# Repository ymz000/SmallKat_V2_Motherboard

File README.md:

# SmallKat_V2 Motherboard

By Keion Bisland
  May 2018

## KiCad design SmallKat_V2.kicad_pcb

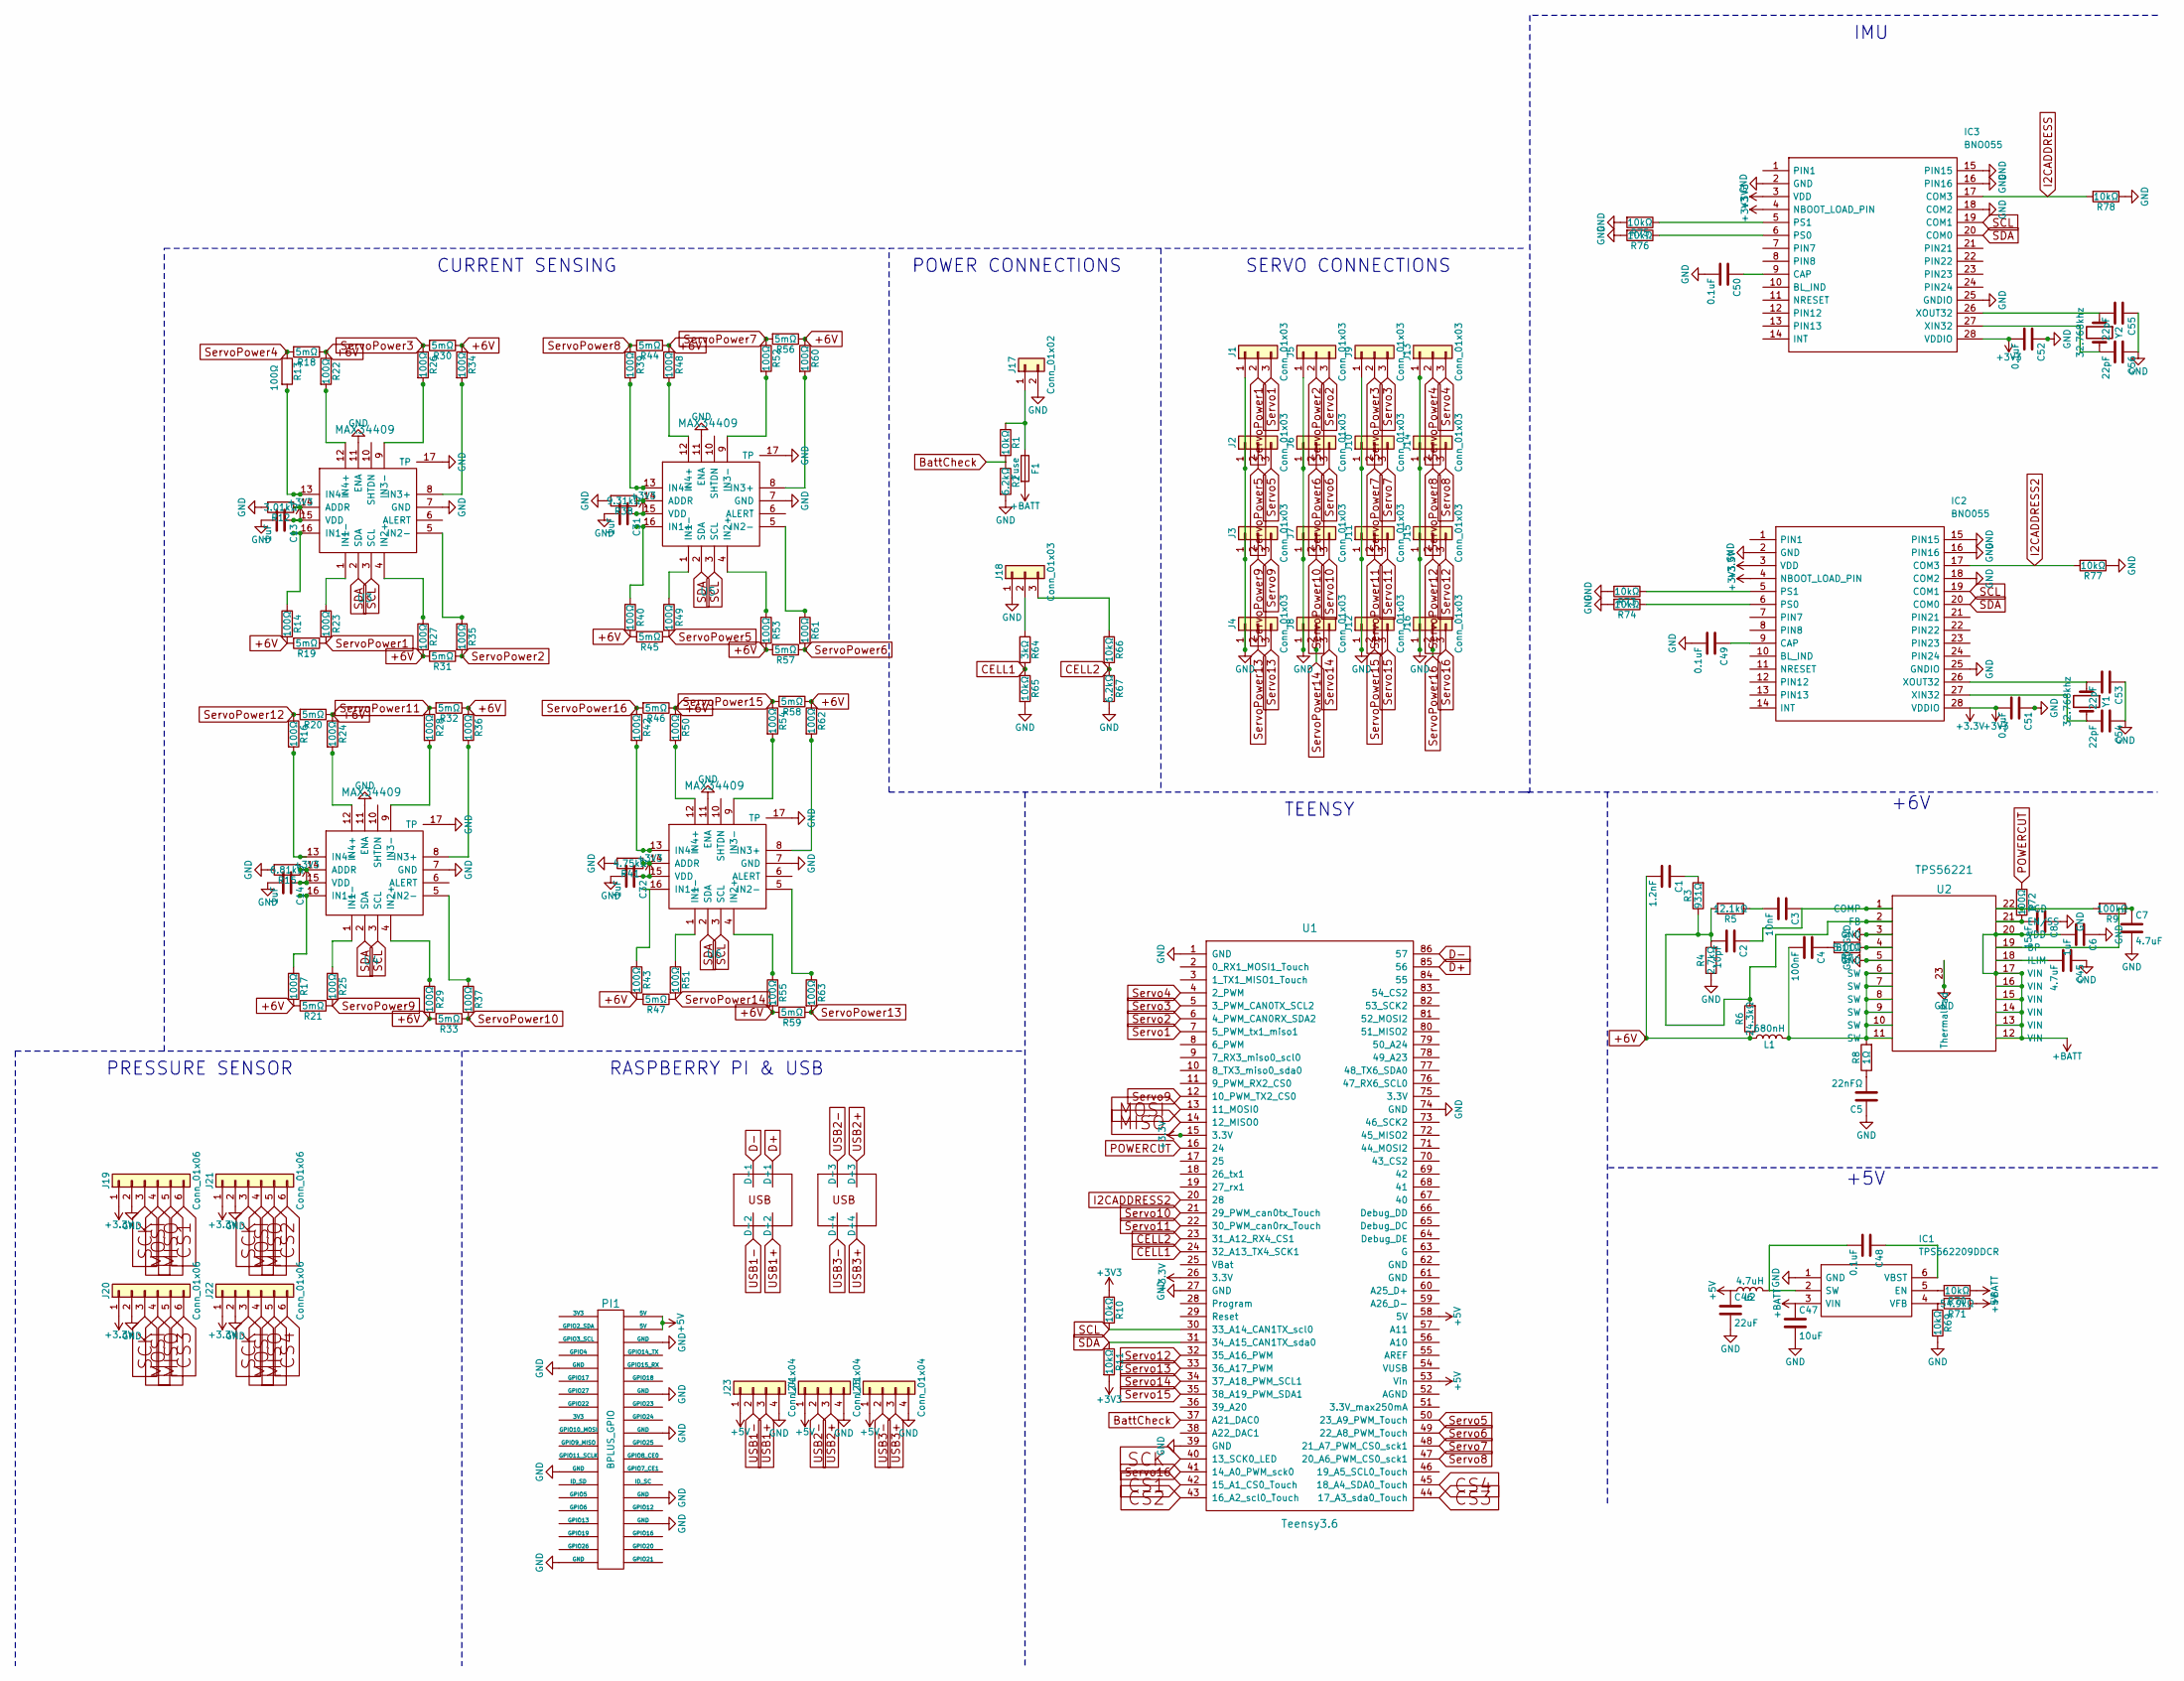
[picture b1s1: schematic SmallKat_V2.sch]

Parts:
C1: 1.2nF; C_0402
C2: 10pF; C_0402
C3: 10nF; C_0402
C4: 100nF; C_0402
C5: 22nFΩ; C_0402
C6: 1uF; C_0603
C7: 4.7uF; C_0603
C8: 15nF; C_0603
C13, C14, C31, C32: 1uF; C_0402
C45: 4.7uF; C_0402
C46: 22uF; C_0603
C47: 10uF; C_0402
C48, C49, C50, C51, C52: 0.1uF; C_0402
C53, C54, C55, C56: 22pF; C_0402
F1: Fuse; Fuse_SMD1206_Reflow
IC1: TPS562209DDCR; SOT95P280X110-6N; Manufacturer_Part_Number TPS562209DDCR
IC2, IC3: BNO055; Manufacturer_Part_Number BNO055
J1, J2, J3, J4, J5, J6, J7, J8, J9, J10, J11, J12, J13, J14, J15, J16, J18: Conn_01x03; Pin_Header_Straight_1x03_Pitch2.54mm
J17: Conn_01x02; Pin_Header_Straight_1x02_Pitch2.54mm
J19, J20, J21, J22: Conn_01x06; Pin_Header_Straight_1x06_Pitch1.00mm
J23, J24, J25: Conn_01x04; Pin_Header_Straight_1x04_Pitch2.00mm
L1: 680nH; L_7.3x7.3_H4.5
L2: 4.7uH; L_0805
PI1: BPLUS_GPIO; Pin_Header_Straight_2x20_Pitch2.54mm
R1, R10, R11, R65, R66, R69, R70, R73, R74, R75, R76, R77, R78: 10kΩ; R_0402
R2, R67: 6.2kΩ; R_0402
R3: 931Ω; R_0402
R4: 2.7kΩ; R_0402
R5: 12.1kΩ; R_0402
R6: 24.3kΩ; R_0402
R7: 5.11Ω; R_0402
R8: 1Ω; R_0402
R9: 100kΩ; R_0402
R12: 3.01kΩ; R_0402
R13, R14, R16, R17, R22, R23, R24, R25, R26, R27, R28, R29, R34, R35, R36, R37, R39, R40, R42, R43, R48, R49, R50, R51, R52, R53, R54, R55, R60, R61, R62, R63, R72: 100Ω; R_0402
R15: 6.81kΩ; R_0402
R18, R19, R20, R21, R30, R31, R32, R33, R44, R45, R46, R47, R56, R57, R58, R59: 5mΩ; R_1210
R38: 9.31kΩ; R_0402
R41: 4.75kΩ; R_0402
R64: 3kΩ; R_0402
R71: 54.9kΩ; R_0402
U1: Teensy3.6; Teensy35_36_custom_2
U2: TPS56221
U3, U4, U5, U6: MAX34409
Y1, Y2: 32.768khz; Crystal_SMD_3215-2pin_3.2x1.5mm

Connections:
+3V3: C13.1, C14.1, C31.1, C32.1, C51.2, C52.2, IC2.3 (VDD), IC2.4 (NBOOT_LOAD_PIN), IC2.28 (VDDIO), IC3.3 (VDD), IC3.4 (NBOOT_LOAD_PIN), IC3.28 (VDDIO), J19.1, J20.1, J21.1, J22.1, R10.1, R11.2, U1.15 (3.3V), U1.26 (3.3V), U3.15 (VDD), U4.15 (VDD), U5.15 (VDD), U6.15 (VDD)
+5V: C46.1, J23.1, J24.1, J25.1, L2.1, PI1.2 (5V), PI1.4 (5V), R71.1, U1.53 (Vin), U1.58 (5V)
+6V: C1.2, L1.1, R6.1, R14.2, R17.2, R18.1, R19.2, R20.1, R21.2, R22.1, R24.1, R27.2, R29.2, R30.1, R31.2, R32.1, R33.2, R34.1, R36.1, R40.2, R43.2, R44.1, R45.2, R46.1, R47.2, R48.1, R50.1, R53.2, R55.2, R56.1, R57.2, R58.1, R59.2, R60.1, R62.1
+BATT: C6.2, C47.1, F1.2, IC1.3 (VIN), R70.1, U2.12 (VIN), U2.13 (VIN), U2.14 (VIN), U2.15 (VIN), U2.16 (VIN), U2.17 (VIN), U2.20 (VDD)
BattCheck: R1.2, R2.1, U1.37 (A21_DAC0)
CELL1: R64.2, R65.1, U1.24 (32_A13_TX4_SCK1)
CELL2: R66.2, R67.1, U1.23 (31_A12_RX4_CS1)
CS1: J19.6, U1.42 (15_A1_CS0_Touch)
CS2: J21.6, U1.43 (16_A2_scl0_Touch)
CS3: J20.6, U1.44 (17_A3_sda0_Touch)
CS4: J22.6, U1.45 (18_A4_SDA0_Touch)
D+: PI1.42 (D+1), U1.85 (56)
D-: PI1.41 (D-1), U1.86 (57)
GND: C5.1, C6.1, C7.2, C8.1, C13.2, C14.2, C31.2, C32.2, C45.1, C46.2, C47.2, C49.2, C50.2, C51.1, C52.1, C53.1, C54.1, C55.1, C56.1, IC1.1 (GND), IC2.2 (GND), IC2.15 (PIN15), IC2.16 (PIN16), IC2.18 (COM2), IC2.25 (GNDIO), IC3.2 (GND), IC3.15 (PIN15), IC3.16 (PIN16), IC3.18 (COM2), IC3.25 (GNDIO), J1.1, J2.1, J3.1, J4.1, J5.1, J6.1, J7.1, J8.1, J9.1, J10.1, J11.1, J12.1, J13.1, J14.1, J15.1, J16.1, J17.2, J18.1, J19.2, J20.2, J21.2, J22.2, J23.4, J24.4, J25.4, PI1.6 (GND), PI1.9 (GND), PI1.14 (GND), PI1.20 (GND), PI1.25 (GND), PI1.30 (GND), PI1.34 (GND), PI1.39 (GND), R2.2, R4.1, R12.2, R15.2, R38.2, R41.2, R65.2, R67.2, R69.2, R73.2, R74.2, R75.2, R76.2, R77.1, R78.1, U1.1 (GND), U1.27 (GND), U1.39 (GND), U1.74 (GND), U2.3 (GND), U2.5 (GND), U2.23 (ThermalPad), U3.7 (GND), U3.11 (ENA), U3.17 (TP), U4.7 (GND), U4.11 (ENA), U4.17 (TP), U5.7 (GND), U5.11 (ENA), U5.17 (TP), U6.7 (GND), U6.11 (ENA), U6.17 (TP)
I2CADDRESS: IC3.17 (COM3), R78.2
I2CADDRESS2: IC2.17 (COM3), R77.2, U1.20 (28)
MISO: J19.5, J20.5, J21.5, J22.5, U1.14 (12_MISO0)
MOSI: J19.4, J20.4, J21.4, J22.4, U1.13 (11_MOSI0)
unnamed: C1.1, R3.2
unnamed: C2.1, C3.1, U2.1 (COMP)
unnamed: C2.2, R3.1, R4.2, R5.2, R6.2, U2.2 (FB)
unnamed: C3.2, R5.1
unnamed: C4.1, R7.2
unnamed: C4.2, L1.2, R8.2, U2.6 (SW), U2.7 (SW), U2.8 (SW), U2.9 (SW), U2.10 (SW), U2.11 (SW)
unnamed: C5.2, R8.1
unnamed: C7.1, R9.1, U2.19 (BP)
unnamed: C8.2, R72.2, U2.21 (EN/SS)
unnamed: C45.2, U2.18 (ILIM)
unnamed: C48.1, IC1.6 (VBST)
unnamed: C48.2, IC1.2 (SW), L2.2
unnamed: C49.1, IC2.9 (CAP)
unnamed: C50.1, IC3.9 (CAP)
unnamed: C53.2, IC2.26 (XOUT32), Y1.1
unnamed: C54.2, IC2.27 (XIN32), Y1.2
unnamed: C55.2, IC3.26 (XOUT32), Y2.1
unnamed: C56.2, IC3.27 (XIN32), Y2.2
unnamed: F1.1, J17.1, R1.1
unnamed: IC1.4 (VFB), R69.1, R71.2
unnamed: IC1.5 (EN), R70.2
unnamed: IC2.5 (PS1), R73.1
unnamed: IC2.6 (PS0), R74.1
unnamed: IC3.5 (PS1), R75.1
unnamed: IC3.6 (PS0), R76.1
unnamed: J18.2, R64.1
unnamed: J18.3, R66.1
unnamed: R7.1, U2.4 (BOOT)
unnamed: R9.2, U2.22 (PGD)
unnamed: R12.1, U3.14 (ADDR)
unnamed: R13.2, U3.13 (IN4-)
unnamed: R14.1, U3.16 (IN1+)
unnamed: R15.1, U4.14 (ADDR)
unnamed: R16.2, U4.13 (IN4-)
unnamed: R17.1, U4.16 (IN1+)
unnamed: R22.2, U3.12 (IN4+)
unnamed: R23.1, U3.1 (IN1-)
unnamed: R24.2, U4.12 (IN4+)
unnamed: R25.1, U4.1 (IN1-)
unnamed: R26.2, U3.9 (IN3-)
unnamed: R27.1, U3.4 (IN2+)
unnamed: R28.2, U4.9 (IN3-)
unnamed: R29.1, U4.4 (IN2+)
unnamed: R34.2, U3.8 (IN3+)
unnamed: R35.1, U3.5 (IN2-)
unnamed: R36.2, U4.8 (IN3+)
unnamed: R37.1, U4.5 (IN2-)
unnamed: R38.1, U5.14 (ADDR)
unnamed: R39.2, U5.13 (IN4-)
unnamed: R40.1, U5.16 (IN1+)
unnamed: R41.1, U6.14 (ADDR)
unnamed: R42.2, U6.13 (IN4-)
unnamed: R43.1, U6.16 (IN1+)
unnamed: R48.2, U5.12 (IN4+)
unnamed: R49.1, U5.1 (IN1-)
unnamed: R50.2, U6.12 (IN4+)
unnamed: R51.1, U6.1 (IN1-)
unnamed: R52.2, U5.9 (IN3-)
unnamed: R53.1, U5.4 (IN2+)
unnamed: R54.2, U6.9 (IN3-)
unnamed: R55.1, U6.4 (IN2+)
unnamed: R60.2, U5.8 (IN3+)
unnamed: R61.1, U5.5 (IN2-)
unnamed: R62.2, U6.8 (IN3+)
unnamed: R63.1, U6.5 (IN2-)
POWERCUT: R72.1, U1.16 (24)
SCK: J19.3, J20.3, J21.3, J22.3, U1.40 (13_SCK0_LED)
SCL: IC2.19 (COM1), IC3.19 (COM1), R10.2, U1.30 (33_A14_CAN1TX_scl0), U3.3 (SCL), U4.3 (SCL), U5.3 (SCL), U6.3 (SCL)
SDA: IC2.20 (COM0), IC3.20 (COM0), R11.1, U1.31 (34_A15_CAN1TX_sda0), U3.2 (SDA), U4.2 (SDA), U5.2 (SDA), U6.2 (SDA)
Servo1: J1.3, U1.7 (5_PWM_tx1_miso1)
Servo2: J5.3, U1.6 (4_PWM_CAN0RX_SDA2)
Servo3: J9.3, U1.5 (3_PWM_CAN0TX_SCL2)
Servo4: J13.3, U1.4 (2_PWM)
Servo5: J2.3, U1.50 (23_A9_PWM_Touch)
Servo6: J6.3, U1.49 (22_A8_PWM_Touch)
Servo7: J10.3, U1.48 (21_A7_PWM_CS0_sck1)
Servo8: J14.3, U1.47 (20_A6_PWM_CS0_sck1)
Servo9: J3.3, U1.12 (10_PWM_TX2_CS0)
Servo10: J7.3, U1.21 (29_PWM_can0tx_Touch)
Servo11: J11.3, U1.22 (30_PWM_can0rx_Touch)
Servo12: J15.3, U1.32 (35_A16_PWM)
Servo13: J4.3, U1.33 (36_A17_PWM)
Servo14: J8.3, U1.34 (37_A18_PWM_SCL1)
Servo15: J12.3, U1.35 (38_A19_PWM_SDA1)
Servo16: J16.3, U1.41 (14_A0_PWM_sck0)
ServoPower1: J1.2, R19.1, R23.2
ServoPower2: J5.2, R31.1, R35.2
ServoPower3: J9.2, R26.1, R30.2
ServoPower4: J13.2, R13.1, R18.2
ServoPower5: J2.2, R45.1, R49.2
ServoPower6: J6.2, R57.1, R61.2
ServoPower7: J10.2, R52.1, R56.2
ServoPower8: J14.2, R39.1, R44.2
ServoPower9: J3.2, R21.1, R25.2
ServoPower10: J7.2, R33.1, R37.2
ServoPower11: J11.2, R28.1, R32.2
ServoPower12: J15.2, R16.1, R20.2
ServoPower13: J4.2, R59.1, R63.2
ServoPower14: J8.2, R47.1, R51.2
ServoPower15: J12.2, R54.1, R58.2
ServoPower16: J16.2, R42.1, R46.2
USB1+: J23.3, PI1.44 (D+2)
USB1-: J23.2, PI1.43 (D-2)
USB2+: J24.3, PI1.46 (D+3)
USB2-: J24.2, PI1.45 (D-3)
USB3+: J25.3, PI1.48 (D+4)
USB3-: J25.2, PI1.47 (D-4)

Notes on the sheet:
IMU
SERVO CONNECTIONS
POWER CONNECTIONS
CURRENT SENSING
TEENSY
+6V
+5V
RASPBERRY PI & USB
PRESSURE SENSOR

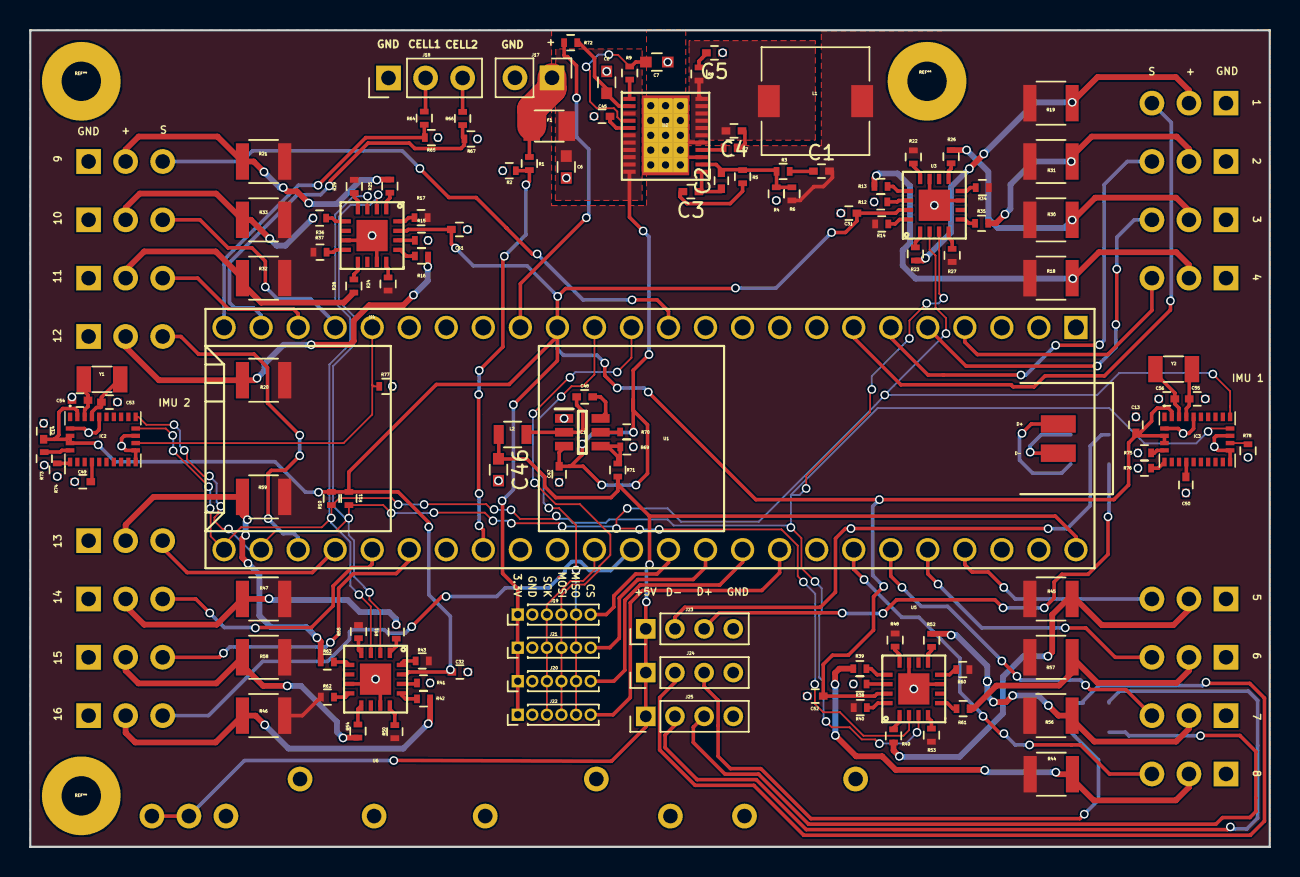
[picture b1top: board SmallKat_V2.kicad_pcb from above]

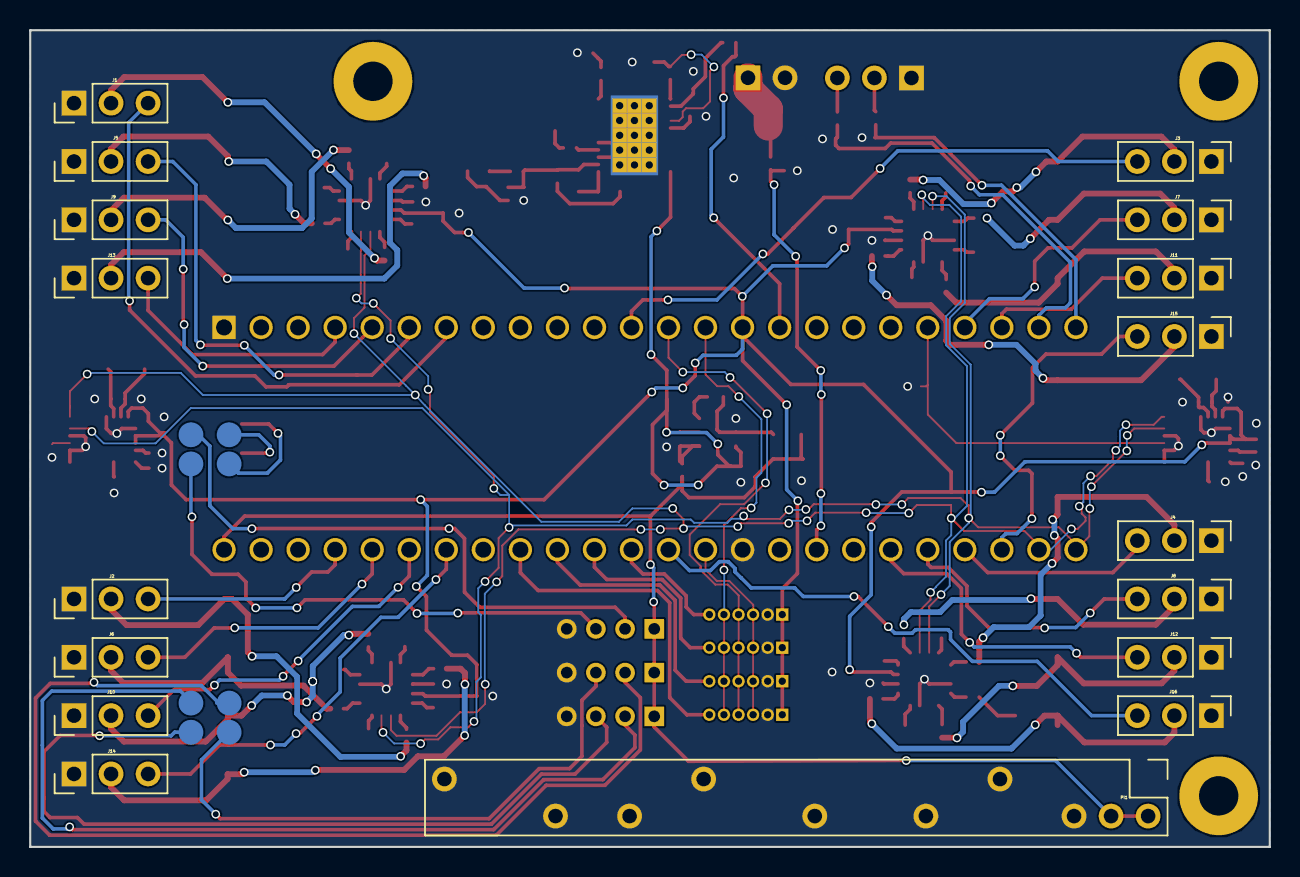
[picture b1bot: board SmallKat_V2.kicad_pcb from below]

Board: 2 copper layers, 85.0 x 56.0 mm, 141 parts (17 on the bottom side), 125 nets.

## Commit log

2018-05-22 All files
2018-06-12 Rev 1
2018-06-12 Removed bad files
2018-06-12 updated read me
